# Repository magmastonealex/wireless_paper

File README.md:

E-Paper Thingy
===

This repository contains source code for the Zephyr application which runs on the e-paper boards I designed.

Additionally, a Rust-based "host" application is in the `host/` subdirectory which acts as a "server" for these displays, providing images to display, over-the-air upgrades, and a small dashboard where you can view status of the fleet of displays.

The two components talk with one another using CoAP on top of a Thread network.

Details on this project are available on [my website](https://alexroth.me/display/). Detailed compilation and setup instructions will come to this repository "at some point". If you really want to make use of anything from here, please feel free to reach out and I'll get to it faster :)

Claude usage
===

Claude contributed to some parts of this project, particularly the CRUD infrastructure and web UI (which I _really_ can't be bothered to write). This was mostly an experiement to understand how Claude can assist me with the parts of personal projects I normally put off and never get to - overall, it was a positive experience, though the output of the tool needed a lot of correction and review. Commits where Claude was used are marked with "Claude:" as a prefix.

OpenThread Credentials
===

There are OpenThread credentials present in src/main.c. These were test credentials I used during initial setup of the boards, and should be changed to match your network. Provisioning of OpenThread datasets is supported over a serial shell and should be done that way wherever possible.

Signing key
===
yes, I know signing_key.pem is public. This is an open-source project, I'm not trying to lock anyone out of any devices. see notes in sysbuild.conf as to how to do this _properly_ if you really care.

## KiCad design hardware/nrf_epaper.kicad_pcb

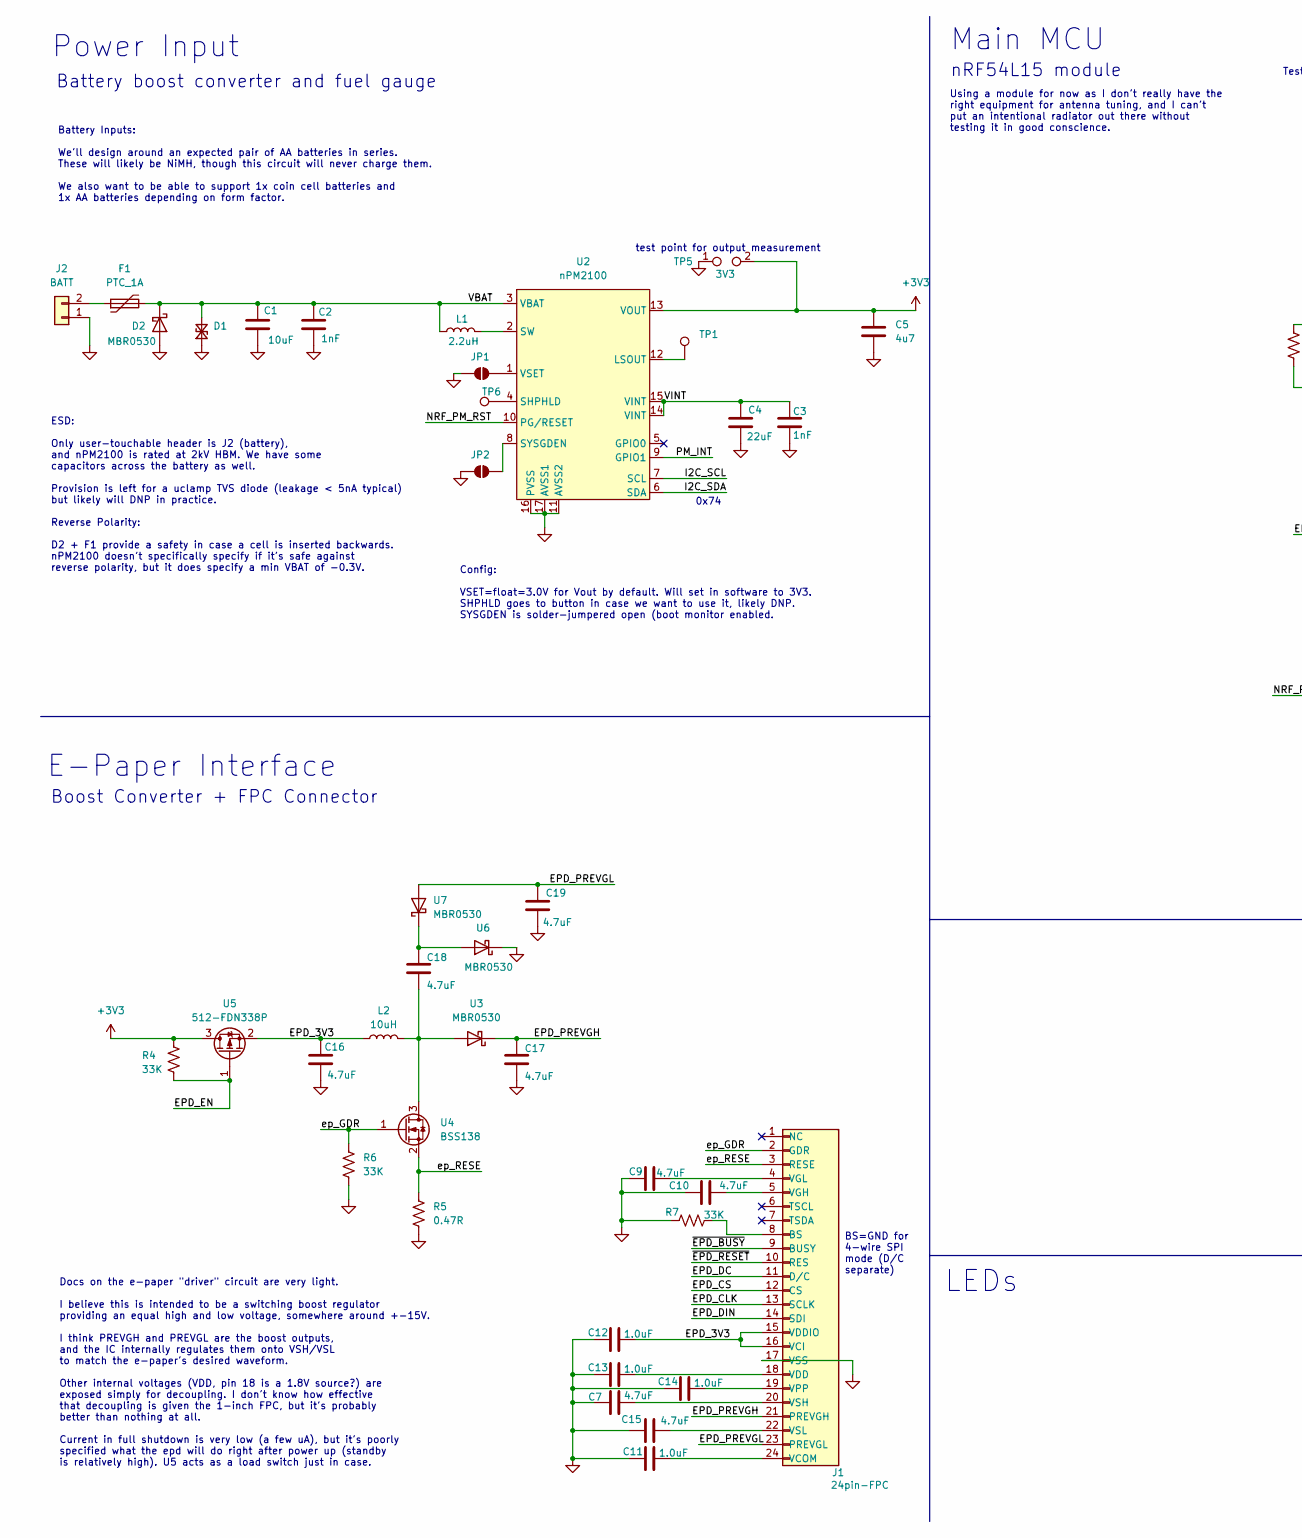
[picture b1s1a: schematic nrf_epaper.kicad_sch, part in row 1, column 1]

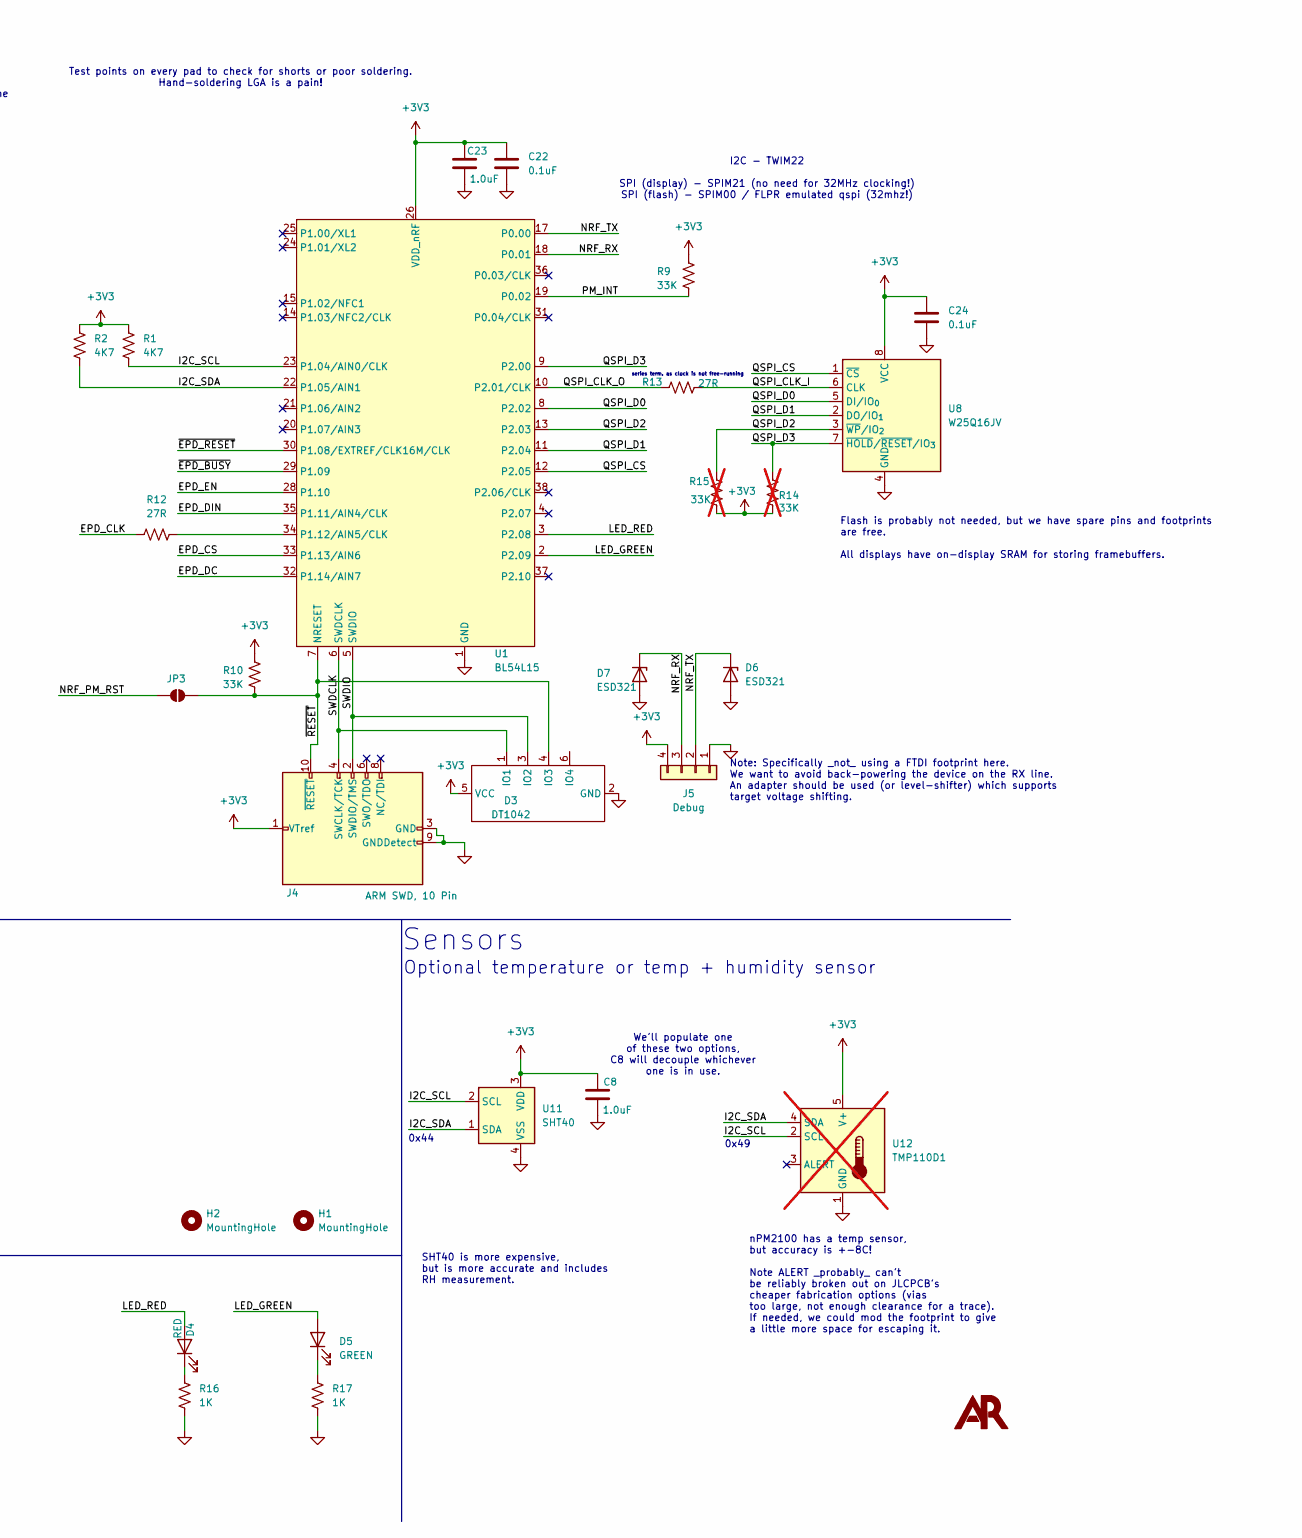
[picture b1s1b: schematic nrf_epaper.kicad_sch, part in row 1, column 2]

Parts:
C1: 10uF; C_0805_2012Metric_Pad1.18x1.45mm_HandSolder
C2, C3: 1nF; C_0603_1608Metric
C4: 22uF; C_0805_2012Metric_Pad1.18x1.45mm_HandSolder
C5: 4u7; C_0805_2012Metric_Pad1.18x1.45mm_HandSolder
C7, C9, C10, C15, C16, C17, C18, C19: 4.7uF; C_1206_3216Metric
C8, C11, C12, C13, C14, C23: 1.0uF; C_0805_2012Metric_Pad1.18x1.45mm_HandSolder
C22, C24: 0.1uF; C_0805_2012Metric_Pad1.18x1.45mm_HandSolder
D1: UCLAMP03351PW.C; D_SOD-882D
D2: MBR0530; D_SOD-123
D3: DT1042; SOT-26
D4: RED; LED_0805_2012Metric_Pad1.15x1.40mm_HandSolder
D5: GREEN; LED_0805_2012Metric_Pad1.15x1.40mm_HandSolder
D6, D7: ESD321; D_SOD-523
F1: PTC_1A; Fuse_1812
H1, H2: MountingHole; MountingHole_2.2mm_M2
J1: 24pin-FPC; AMP_F331_24pin
J2: BATT; PinHeader_1x02_P2.54mm_Vertical
J4: ARM SWD, 10 Pin; ARM_SWD_10pin_SMD
J5: Debug; PinSocket_1x04_P1.27mm_Vertical
JP1, JP2, JP3: SolderJumper_2_Open; SolderJumper-2_P1.3mm_Open_TrianglePad1.0x1.5mm
L1: 2.2uH; L_1008_2520Metric
L2: 10uH; L_Taiyo-Yuden_NR-40xx_HandSoldering
R1, R2: 4K7; R_0805_2012Metric_Pad1.20x1.40mm_HandSolder
R4, R6, R7, R9, R10: 33K; R_0805_2012Metric_Pad1.20x1.40mm_HandSolder
R5: 0.47R; R_0805_2012Metric_Pad1.20x1.40mm_HandSolder
R12, R13: 27R; R_0603_1608Metric_Pad0.98x0.95mm_HandSolder
R14, R15: 33K; R_0805_2012Metric_Pad1.20x1.40mm_HandSolder; not fitted
R16, R17: 1K; R_0805_2012Metric_Pad1.20x1.40mm_HandSolder
REF1: Touchmark
TP1: TestPoint; TestPoint_Pad_D1.0mm
TP5: 3V3; PinHeader_2x01_P2.54mm_Vertical
TP6: TestPoint; TestPoint_Pad_D2.0mm
U1: BL54L15
U2: nPM2100; QFN-16-1EP_4x4mm_P0.65mm_EP2.5x2.5mm_ThermalVias
U3, U6, U7: MBR0530; D_SOD-123
U4: BSS138; SOT-23
U5: 512-FDN338P; SOT-23
U8: W25Q16JV; Winbond_USON-8_UU
U11: SHT40; Sensirion_DFN-4_1.5x1.5mm_P0.8mm_SHT4x_NoCentralPad
U12: TMP110D1; Texas_X2SON-5_0.8x0.8mm_P0.48mm; not fitted

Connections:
+3V3: C5.1, C8.2, C22.1, C23.2, C24.1, D3.5 (VCC), J4.1 (VTref), J5.4, R1.1, R2.1, R4.1, R9.1, R10.1, R14.2, R15.2, TP5.2, U1.26 (VDD_nRF), U2.13 (VOUT), U5.3 (D), U8.8 (VCC), U11.3 (VDD), U12.5 (V+)
/EPD_3V3: C12.2, C16.2, J1.15 (VDDIO), J1.16 (VCI), L2.1, U5.2 (S)
/EPD_CLK: J1.13 (SCLK), R12.1
/EPD_CS: J1.12 (CS), U1.33 (P1.13/AIN6); also elsewhere on the board
/EPD_DC: J1.11 (D/C), U1.32 (P1.14/AIN7); also elsewhere on the board
/EPD_DIN: J1.14 (SDI), U1.35 (P1.11/AIN4/CLK); also elsewhere on the board
/EPD_EN: R4.2, U1.28 (P1.10), U5.1 (G); also elsewhere on the board
/EPD_PREVGH: C17.1, J1.21 (PREVGH), U3.1 (K)
/EPD_PREVGL: C19.2, J1.23 (PREVGL), U7.2 (A)
/I2C_SCL: R1.2, U1.23 (P1.04/AIN0/CLK), U2.7 (SCL), U11.2 (SCL), U12.2 (SCL)
/I2C_SDA: R2.2, U1.22 (P1.05/AIN1), U2.6 (SDA), U11.1 (SDA), U12.4 (SDA)
/LED_GREEN: D5.2 (A), U1.2 (P2.09)
/LED_RED: D4.2 (A), U1.3 (P2.08)
/NRF_PM_RST: JP3.2 (B), U2.10 (PG/RESET)
/NRF_RX: D7.1 (K), J5.3, U1.18 (P0.01)
/NRF_TX: D6.1 (K), J5.2, U1.17 (P0.00)
/PM_INT: R9.2, U1.19 (P0.02), U2.9 (GPIO1)
/QSPI_CLK_I: R13.2, U8.6 (CLK)
/QSPI_CLK_O: R13.1, U1.10 (P2.01/CLK)
/QSPI_CS: U1.12 (P2.05), U8.1 (~CS)
/QSPI_D0: U1.8 (P2.02), U8.5 (DI/IO_{0})
/QSPI_D1: U1.11 (P2.04), U8.2 (DO/IO_{1})
/QSPI_D2: R15.1, U1.13 (P2.03), U8.3 (~WP/IO_{2})
/QSPI_D3: R14.1, U1.9 (P2.00), U8.7 (~HOLD/~RESET/IO_{3})
/SWDCLK: D3.1 (IO1), J4.4 (SWCLK/TCK), U1.6 (SWDCLK)
/SWDIO: D3.3 (IO2), J4.2 (SWDIO/TMS), U1.5 (SWDIO)
/VBAT: C1.1, C2.1, D1.2 (A2), D2.1 (K), F1.2, L1.1, U2.3 (VBAT)
/VINT: C3.1, C4.1, U2.14 (VINT), U2.15 (VINT)
/ep_GDR: J1.2 (GDR), R6.1, U4.1 (G)
/ep_RESE: J1.3 (RESE), R5.1, U4.2 (S)
/~EPD_BUSY: J1.9 (BUSY), U1.29 (P1.09); also elsewhere on the board
/~EPD_RESET: J1.10 (RES), U1.30 (P1.08/EXTREF/CLK16M/CLK); also elsewhere on the board
/~RESET: D3.4 (IO3), J4.10 (~RESET), JP3.1 (A), R10.2, U1.7 (NRESET)
GND: C1.2, C2.2, C3.2, C4.2, C5.2, C7.1, C8.1, C9.1, C10.1, C11.1, C12.1, C13.1, C14.1, C15.1, C16.1, C17.2, C19.1, C22.2, C23.1, C24.2, D1.1 (A1), D2.2 (A), D3.2 (GND), D6.2 (A), D7.2 (A), J1.17 (VSS), J2.1, J4.3 (GND), J4.5 (GND), J4.9 (GNDDetect), J5.1, JP1.2 (B), JP2.2 (B), R5.2, R6.2, R7.1, R16.2, R17.2, TP5.1, U1.1 (GND), U1.16 (GND), U1.27 (GND), U1.39 (GND), U2.11 (AVSS2), U2.16 (PVSS), U2.17 (AVSS1), U6.1 (K), U8.4 (GND), U11.4 (VSS), U12.1 (GND)
unnamed: D4.1 (K), R16.1
unnamed: D5.1 (K), R17.1
unnamed: J1.8 (BS), R7.2
unnamed: C11.2, J1.24 (VCOM)
unnamed: C13.2, J1.18 (VDD)
unnamed: C10.2, J1.5 (VGH)
unnamed: C9.2, J1.4 (VGL)
unnamed: C14.2, J1.19 (VPP)
unnamed: C7.2, J1.20 (VSH)
unnamed: C15.2, J1.22 (VSL)
unnamed: F1.1, J2.2
unnamed: JP1.1 (A), U2.1 (VSET)
unnamed: JP2.1 (A), U2.8 (SYSGDEN)
unnamed: R12.2, U1.34 (P1.12/AIN5/CLK)
unnamed: TP1.1, U2.12 (LSOUT)
unnamed: TP6.1, U2.4 (SHPHLD)
unnamed: L1.2, U2.2 (SW)
unnamed: C18.2, L2.2, U3.2 (A), U4.3 (D)
unnamed: C18.1, U6.2 (A), U7.1 (K)

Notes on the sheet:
test point for output measurement
Test points on every pad to check for shorts or poor soldering. Hand-soldering LGA is a pain!
Optional temperature or temp + humidity sensor
Battery Inputs: We'll design around an expected pair of AA batteries in series. These will likely be NiMH, though this circuit will never charge them. We also want to be able to support 1x coin cell batteries and 1x AA batteries depending on form factor.
LEDs
Main MCU
ESD: Only user-touchable header is J2 (battery), and nPM2100 is rated at 2kV HBM. We have some capacitors across the battery as well. Provision is left for a uclamp TVS diode (leakage < 5nA typical) but likely will DNP in practice. Reverse Polarity: D2 + F1 provide a safety in case a cell is insert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
0x44
SHT40 is more expensive, but is more accurate and includes RH measurement.
Note: Specifically _not_ using a FTDI footprint here. We want to avoid back-powering the device on the RX line. An adapter should be used (or level-shifter) which supports target voltage shifting.
Sensors
series term. as clock is not free-running
E-Paper Interface
0x74
Power Input
I2C - TWIM22 SPI (display) - SPIM21 (no need for 32MHz clocking!) SPI (flash) - SPIM00 / FLPR emulated qspi (32mhz!)
BS=GND for 4-wire SPI mode (D/C separate)
nPM2100 has a temp sensor, but accuracy is +-8C! Note ALERT _probably_ can't be reliably broken out on JLCPCB's cheaper fabrication options (vias too large, not enough clearance for a trace). If needed, we could mod the footprint to give a little more space for escaping it.
Using a module for now as I don't really have the right equipment for antenna tuning, and I can't put an intentional radiator out there without testing it in good conscience.
Config: VSET=float=3.0V for Vout by default. Will set in software to 3V3. SHPHLD goes to button in case we want to use it, likely DNP. SYSGDEN is solder-jumpered open (boot monitor enabled.
0x49
We'll populate one of these two options, C8 will decouple whichever one is in use.
Boost Converter + FPC Connector
nRF54L15 module
Flash is probably not needed, but we have spare pins and footprints are free. All displays have on-display SRAM for storing framebuffers.
Docs on the e-paper "driver" circuit are very light. I believe this is intended to be a switching boost regulator providing an equal high and low voltage, somewhere around +-15V. I think PREVGH and PREVGL are the boost outputs, and the IC internally regulates them onto VSH/VSL to match the e-paper'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
Battery boost converter and fuel gauge

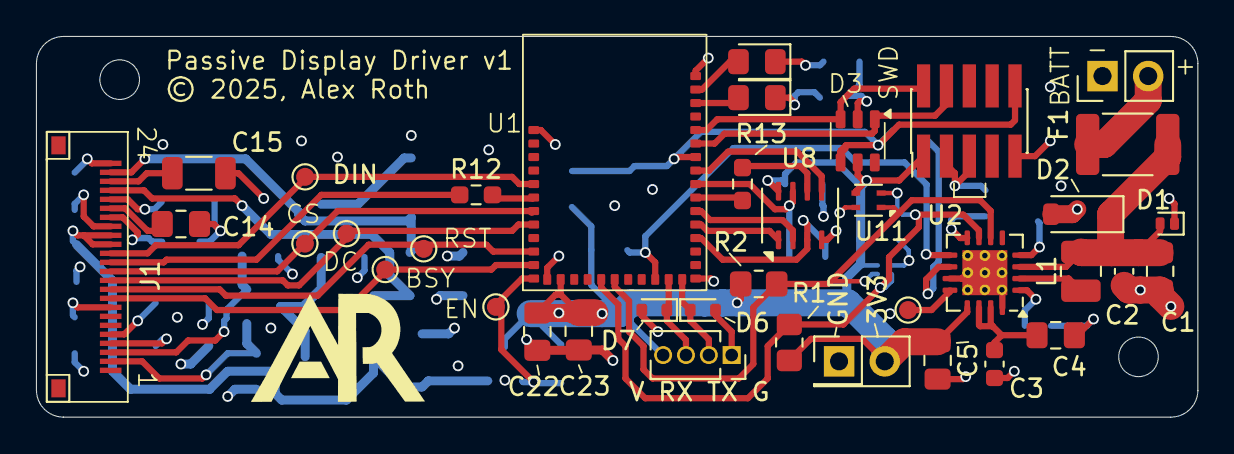
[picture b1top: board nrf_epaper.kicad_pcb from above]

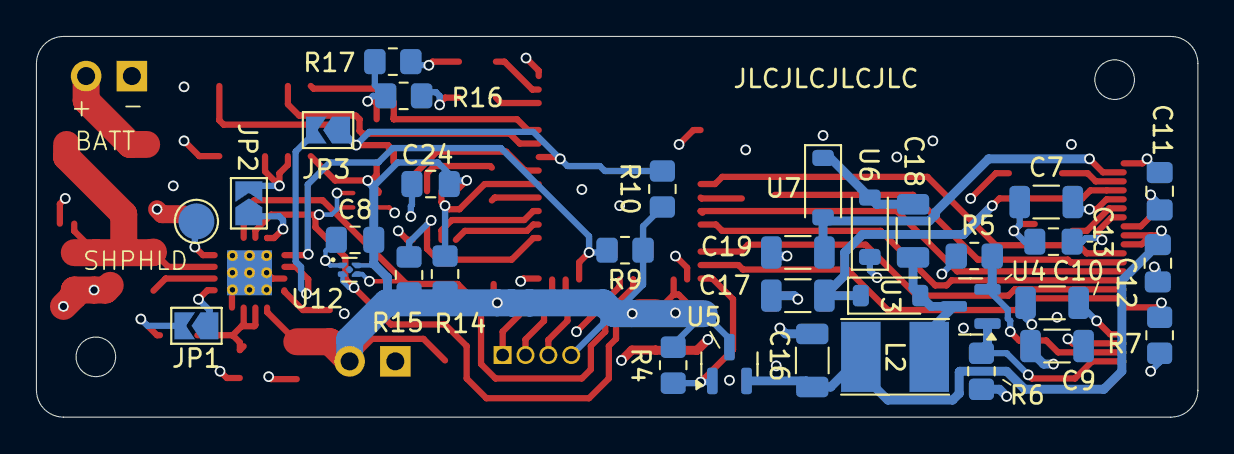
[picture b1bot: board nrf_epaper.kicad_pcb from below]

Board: 4 copper layers, 64.5 x 21.2 mm, 74 parts (33 on the bottom side), 53 nets.

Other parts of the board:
TP2, TP3, TP4, TP7, TP9, TP10: TestPoint; TestPoint_Pad_D1.0mm

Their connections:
/EPD_CS: TP9.1; also elsewhere on the board
/EPD_DC: TP10.1; also elsewhere on the board
/EPD_DIN: TP7.1; also elsewhere on the board
/EPD_EN: TP4.1; also elsewhere on the board
/~EPD_BUSY: TP3.1; also elsewhere on the board
/~EPD_RESET: TP2.1; also elsewhere on the board

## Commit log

2025-08-27 initial commit, porting worked??
2025-08-31 mostly wired up
2025-08-31 Initial draft completed
2025-08-31 Initial placement
2025-09-01 one routing attempt
2025-09-02 I think this new layout will work better?
2025-09-02 layout is taking shape
2025-09-02 one placement option for epaper drive
2025-09-02 I think it'll work?
2025-09-02 Routed, needs review + silks fix
2025-09-02 Silkscreen is done
2025-09-02 tweaks before mfg
2025-09-05 Builds, openthread comes up at boot. Don't like the flash wear caused by settings + OpenThread.
2025-09-05 progress
2025-09-07 FOTA over thread + CoAP works
2025-09-09 renders an image (this was a lot of work to come full circle lol)
2025-09-10 Working using heatshrink
2025-09-11 working on dk, now disable lfxo
2025-09-11 working no low freq oscillator
2025-09-11 combine into one dts
2025-09-11 it flashes on the new board
2025-09-11 omg it works on the real board
2025-09-12 npm2100 is working
2025-09-12 help with 3v3 voltage spike when epd boost turns off
2025-09-14 cleaning up host app
2025-09-15 temp db in progress
2025-09-15 db temp
2025-09-19 CLAUDE: claude has started on the DB and done some weird things
2025-09-19 CLAUDE: claude progress adding DB and business logic
2025-09-19 CLAUDE: wow claude did more than I thought it would
2025-09-19 fixup cargo warnings, I don't care about clippy :)
2025-09-19 Add some plumbing to serve up firmware, keep serving image data
2025-09-19 add cbor encoding to fw image
2025-09-19 fixup tests (again)
2025-09-19 fixup tests
2025-09-19 add vbat, tidy up some code
2025-09-20 Add coap request helper and proper CBOR decode/encode routines
2025-09-20 heartbeats are being sent, imgs are working properly
2025-09-20 Heartbeats are finally working. Full FOTA flow is next, then dashboard rendering, then other display sizes
2025-09-20 Firmware version 1 is completed. FOTA works, as does configurable sleep intervals and heartbeating.
2025-09-20 Add details on next steps on FW side
2025-09-21 Sleep if not connected within 60 seconds. Adjust window for heartbeat to account for inaccurate timing
2025-09-22 fetch images automatically
2025-09-22 try to get things running on a devkit again for spi based epaper dev
2025-09-23 try to get things running on devkit, won't quite boot
2025-09-23 builds for both, tested somewhat on DK. Need to test on real board now
2025-10-02 Add generic epaper driver in, update devkit DTS. Send metadata along with image request to describe what type of image should be received
2025-10-02 start on minimal settings wrapper
2025-10-05 starting to deploy to real boards
2025-10-05 Claude + some manual help: Convert images into 2bpp or 1bpp format depending on display type
2025-10-05 All devices mostly working - 3.5 inch epaper is rotated 90 from what I expected
2025-10-05 Plumb rotation through, all displays render now
2025-10-05 Claude: Fetch images for each display
2025-10-05 Claude: Add plumbing for rotation per-display
2025-10-05 Claude: Update plumbing to support a per-display image URL and display type tracking.
2025-10-05 Tidy up logging, make mcuboot start up
2025-10-05 Clean up repo - remove old binaries
2025-10-05 Add licensing for heatshrink
2025-10-05 try to fix image
2025-10-11 Allow slotting in custom TLV data

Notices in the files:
hardware/nrf_epaper.kicad_pcb:
© 2025, Alex Roth
